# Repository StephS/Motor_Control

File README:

This board is an H-Bridge DC Motor Controller. The ratings are yet to be determined (requires calculation).
The end goal is to support a 12v 60A Electric Trolling Motor for a boat. This board does NOT have a PWM source (that will be a separate board).
Licence is CC-BY-SA

This board is a PROTOTYPE until the design is built and tested.

The bottom traces need Solid wire soldered on to improve current capacity. Please read the Allegro A3941 Datasheet for usage.

If you'd like to donate so I can buy the full version of Eagle, and make more cool stuff, please contact me through Google+

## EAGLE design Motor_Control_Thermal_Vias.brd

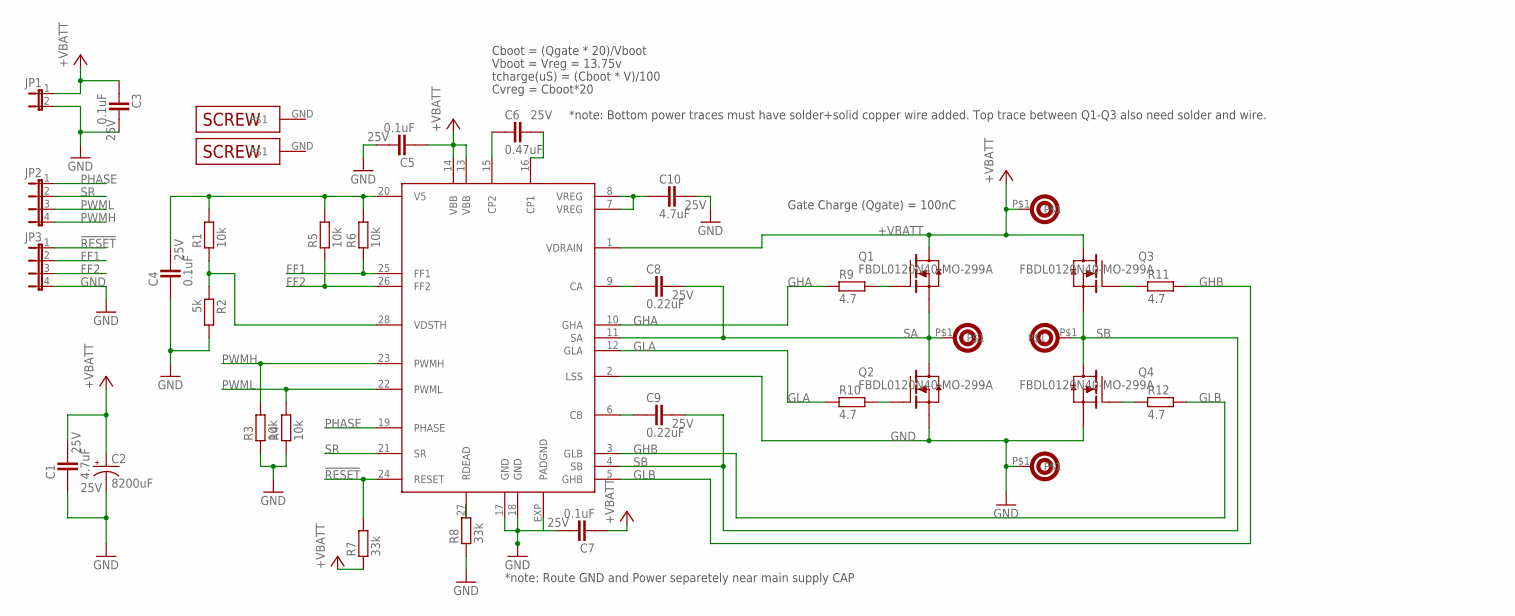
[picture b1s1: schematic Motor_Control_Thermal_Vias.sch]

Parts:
C1, C10: 4.7uF; CAPC1608X92N; VOLTAGE 25V
C2: 8200uF; CAP-10-22; VOLTAGE 25V
C3, C5, C7: 0.1uF; CAPC1608X92N; VOLTAGE 25V
C4: 0.1uF; CAPC_0603_LONG; VOLTAGE 25V
C6: 0.47uF; CAPC1608X92N; VOLTAGE 25V
C8, C9: 0.22uF; CAPC_0603_LONG; VOLTAGE 25V
J1, J2, J3, J4: 63971-1-QC_TAB-RA; QUICK_CONN_TAB-RA
JP1: JP1E; JP1
JP2, JP3: JP4E; JP4
Q1, Q2, Q3, Q4: FBDL0120N40-MO-299A; MO-299
R1, R3, R4, R5, R6: 10k; RESC1608X55N
R2: 5k; RESC1608X55N
R7, R8: 33k; RESC1608X55N
R9, R10, R11, R12: 4.7; RESC1608X55N
SCREW1, SCREW2: SCREW-4MM; PLATEDSCREW-4MM
U1: A3941-TSSOP28-LP; TSSOP28-LP

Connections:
!RESET: JP3.1, R7.2, U1.24 (RESET)
+VBATT: C1.2, C2.+, C3.1, C5.1, C7.1, J2.P$1, JP1.1, Q1.P$9 (D), Q3.P$9 (D), R7.1, U1.1 (VDRAIN), U1.13 (VBB), U1.14 (VBB)
FF1: JP3.2, R6.1, U1.25 (FF1)
FF2: JP3.3, R5.1, U1.26 (FF2)
GHA: R9.1, U1.10 (GHA)
GHB: R11.2, U1.5 (GHB)
GLA: R10.1, U1.12 (GLA)
GLB: R12.2, U1.3 (GLB)
GND: C1.1, C2.-, C3.2, C4.1, C5.2, C7.2, C10.2, J4.P$1, JP1.2, JP3.4, Q2.P$2 (S), Q2.P$3 (S), Q2.P$4 (S), Q2.P$5 (S), Q2.P$6 (S), Q2.P$7 (S), Q2.P$8 (S), Q4.P$2 (S), Q4.P$3 (S), Q4.P$4 (S), Q4.P$5 (S), Q4.P$6 (S), Q4.P$7 (S), Q4.P$8 (S), R2.2, R3.1, R4.1, R8.1, U1.2 (LSS), U1.17 (GND), U1.18 (GND), U1.EXP (PADGND)
unnamed: Q1.P$1 (G), R9.2
unnamed: Q2.P$1 (G), R10.2
unnamed: Q4.P$1 (G), R12.1
unnamed: Q3.P$1 (G), R11.1
unnamed: C10.1, U1.7 (VREG), U1.8 (VREG)
unnamed: C8.1, U1.9 (CA)
unnamed: R1.1, R2.1, U1.28 (VDSTH)
unnamed: C9.1, U1.6 (CB)
unnamed: R8.2, U1.27 (RDEAD)
unnamed: C6.1, U1.15 (CP2)
unnamed: C6.2, U1.16 (CP1)
PHASE: JP2.1, U1.19 (PHASE)
PWMH: JP2.4, R3.2, U1.23 (PWMH)
PWML: JP2.3, R4.2, U1.22 (PWML)
SA: C8.2, J1.P$1, Q1.P$2 (S), Q1.P$3 (S), Q1.P$4 (S), Q1.P$5 (S), Q1.P$6 (S), Q1.P$7 (S), Q1.P$8 (S), Q2.P$9 (D), U1.11 (SA)
SB: C9.2, J3.P$1, Q3.P$2 (S), Q3.P$3 (S), Q3.P$4 (S), Q3.P$5 (S), Q3.P$6 (S), Q3.P$7 (S), Q3.P$8 (S), Q4.P$9 (D), U1.4 (SB)
SR: JP2.2, U1.21 (SR)
V5: C4.2, R1.2, R5.2, R6.2, U1.20 (V5)

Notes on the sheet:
Cboot = (Qgate * 20)/Vboot
Vboot = Vreg = 13.75v
Gate Charge (Qgate) = 100nC
tcharge(uS) = (Cboot * V)/100
Cvreg = Cboot*20
*note: Route GND and Power separetely near main supply CAP
*note: Bottom power traces must have solder+solid copper wire added. Top trace between Q1-Q3 also need solder and wire.

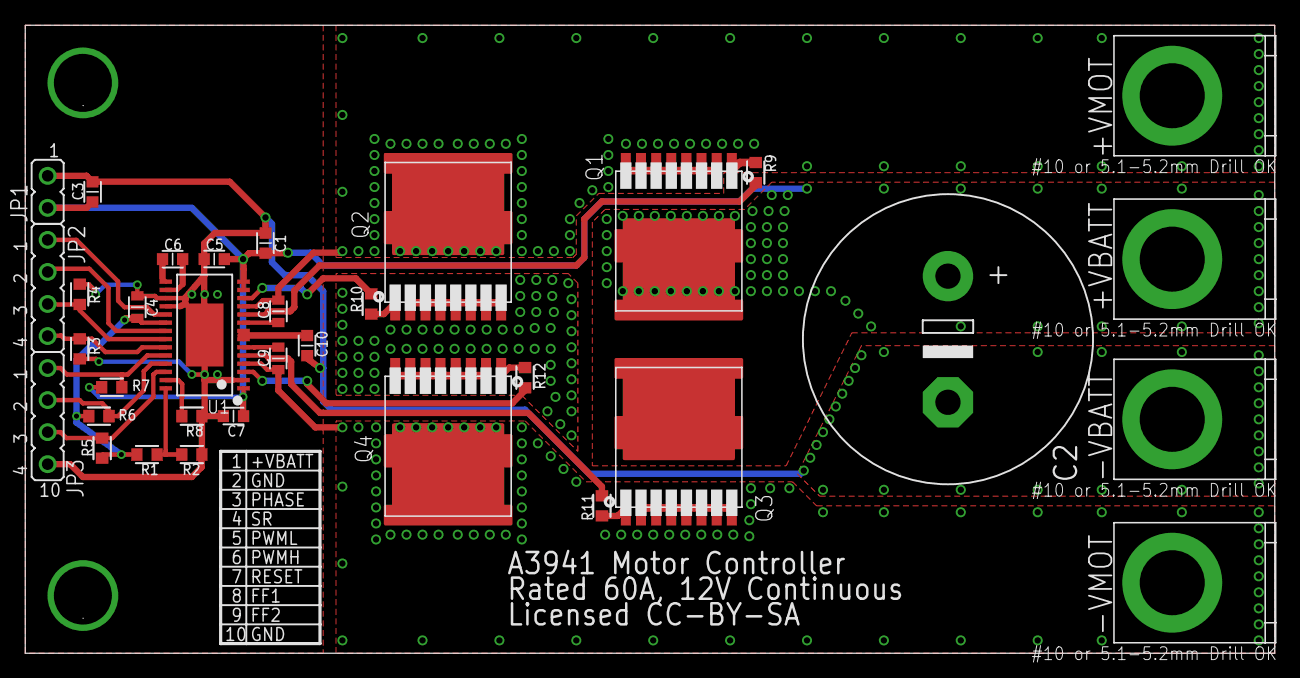
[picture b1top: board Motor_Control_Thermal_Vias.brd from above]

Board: 2 copper layers, 99.1 x 49.8 mm, 36 parts (0 on the bottom side), 27 nets.

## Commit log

2015-06-08 :space_invader: Added .gitattributes & .gitignore files
2015-06-08 First board revision.
    The gate resistors need to be calculated. Everything else is fine. (I
    Hope)
2015-06-08 Fixed the solder mask and Gate resistors
    The soldermask on the bottom side has been changed so there is at least
    20 mils covering the traces. this should prevent shorts.
    The gate resistors are now 4.7 Ohm. I'm not 100% sure this is correct,
    might change to 10 Ohm if I see issues.
2015-06-09 More Via's!
    It can't be a bad thing to add more via's to improve thermals. I also
    added another CAP to improve noise. Silkscreen is updated and the board
    is ready for production!

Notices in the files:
Motor_Control_Thermal_Vias.brd:
Licensed CC-BY-SA
